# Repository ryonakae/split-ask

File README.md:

# Split ASK
Split 60% Apple Standard Keyboard (M0116)

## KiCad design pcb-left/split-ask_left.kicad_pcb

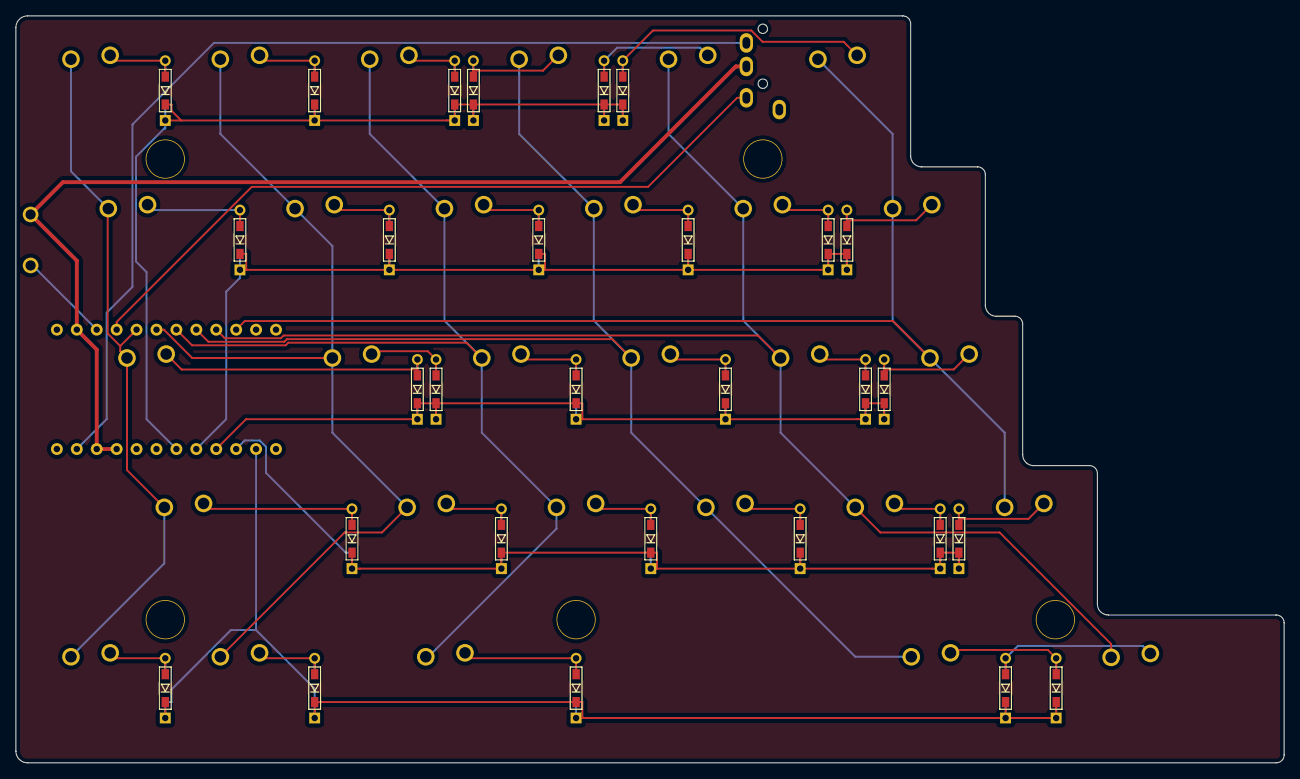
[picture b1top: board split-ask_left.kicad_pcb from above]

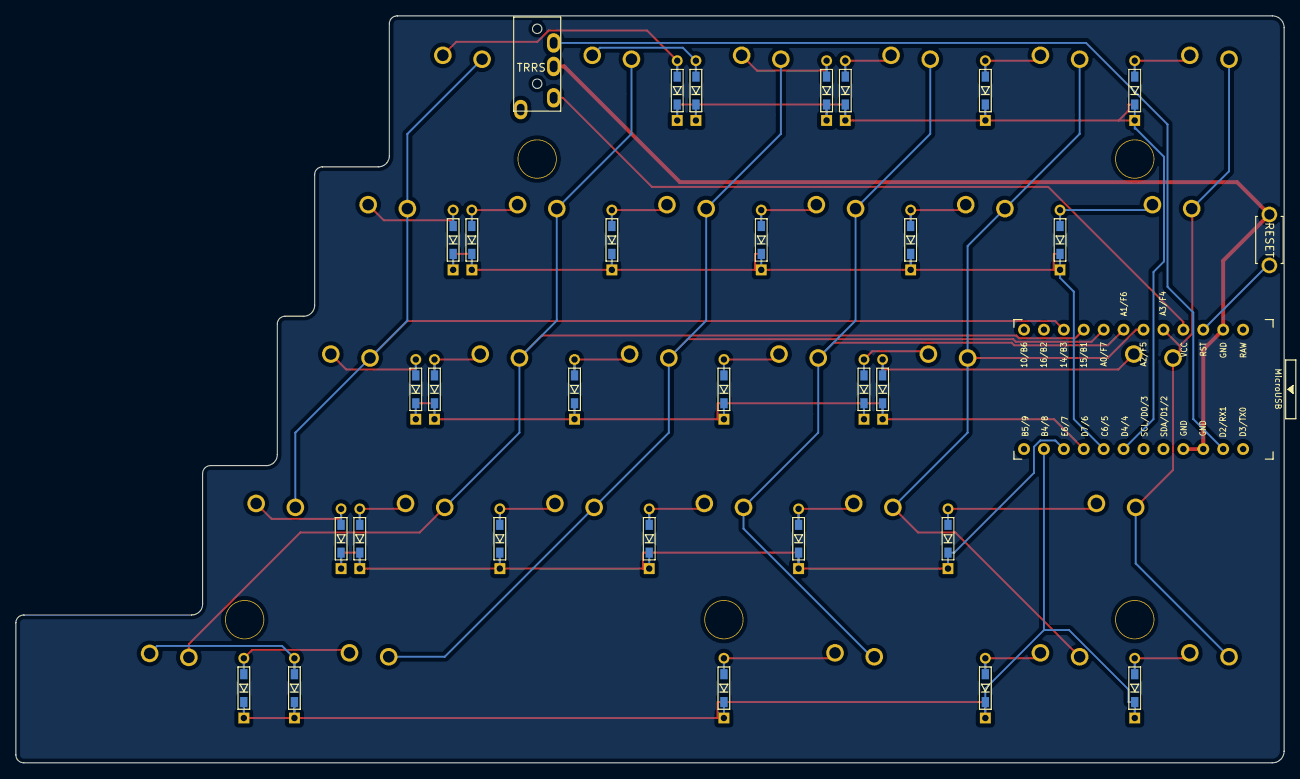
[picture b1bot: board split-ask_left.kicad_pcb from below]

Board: 2 copper layers, 161.7 x 95.2 mm, 66 parts (3 on the bottom side), 44 nets.

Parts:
D1, D2, D3, D4, D5, D6, D7, D8, D9, D10, D11, D12, D13, D14, D15, D16, D17, D18, D19, D20, D21, D22, D23, D24, D25, D26, D27, D28, D29: D; D3_TH_SMD
HOLE1, HOLE3, HOLE4, HOLE5: HOLE
HOLE2: Val**; HOLE
J1: MJ-4PP-9; MJ-4PP-9_1side
RST1: SW_PUSH; ResetSW_1side
SW1, SW2, SW3, SW4, SW5, SW6, SW8, SW9, SW10, SW11, SW12, SW14, SW15, SW16, SW17, SW18, SW20, SW21, SW22, SW23, SW24, SW25, SW26, SW28, SW29: SW_PUSH; ALPS-1U
SW7: SW_PUSH; ALPS-1.5U
SW13, SW27: SW_PUSH; ALPS-1.75U
SW19: SW_PUSH; ALPS-2.25U
U1: ProMicro; ProMicro_v3

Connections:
GND: J1.C, RST1.2, U1.3, U1.4, U1.23
unnamed: D1.2, SW1.2
unnamed: D2.2, SW2.2
unnamed: D3.2, SW3.2
unnamed: D4.2, SW4.2
unnamed: D5.2, SW5.2
unnamed: D6.2, SW6.2
unnamed: D7.2, SW7.2
unnamed: D8.2, SW8.2
unnamed: D9.2, SW9.2
unnamed: D10.2, SW10.2
unnamed: D11.2, SW11.2
unnamed: D12.2, SW12.2
unnamed: D13.2, SW13.2
unnamed: D14.2, SW14.2
unnamed: D15.2, SW15.2
unnamed: D16.2, SW16.2
unnamed: D17.2, SW17.2
unnamed: D18.2, SW18.2
unnamed: D19.2, SW19.2
unnamed: D20.2, SW20.2
unnamed: D21.2, SW21.2
unnamed: D22.2, SW22.2
unnamed: D23.2, SW23.2
unnamed: D24.2, SW24.2
unnamed: D25.2, SW25.2
unnamed: D26.2, SW26.2
unnamed: D27.2, SW27.2
unnamed: D28.2, SW28.2
unnamed: D29.2, SW29.2
VCC: J1.D, U1.21
col0: SW1.1, SW7.1, SW13.1, SW19.1, SW25.1, U1.20
col1: SW2.1, SW8.1, SW14.1, SW20.1, SW26.1, U1.19
col2: SW3.1, SW9.1, SW15.1, SW21.1, SW27.1, U1.18
col3: SW4.1, SW10.1, SW16.1, SW22.1, SW28.1, U1.17
col4: SW5.1, SW11.1, SW17.1, SW23.1, SW29.1, U1.16
col5: SW6.1, SW12.1, SW18.1, SW24.1, U1.15
data: J1.B, U1.2
reset: RST1.1, U1.22
row0: D1.1, D2.1, D3.1, D4.1, D5.1, D6.1, U1.7
row1: D7.1, D8.1, D9.1, D10.1, D11.1, D12.1, U1.8
row2: D13.1, D14.1, D15.1, D16.1, D17.1, D18.1, U1.9
row3: D19.1, D20.1, D21.1, D22.1, D23.1, D24.1, U1.10
row4: D25.1, D26.1, D27.1, D28.1, D29.1, U1.11

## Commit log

2019-07-26 add submodules
2019-07-27 left pcb wip
2019-07-28 add submodule
2019-07-29 routing
2019-08-06 export
2019-08-22 plate v2 wip
2019-08-22 update plate
2019-08-22 update both hand plate
2019-08-22 add acrylic data
2019-08-27 update acrylic plate data
2019-09-04 update plate data
